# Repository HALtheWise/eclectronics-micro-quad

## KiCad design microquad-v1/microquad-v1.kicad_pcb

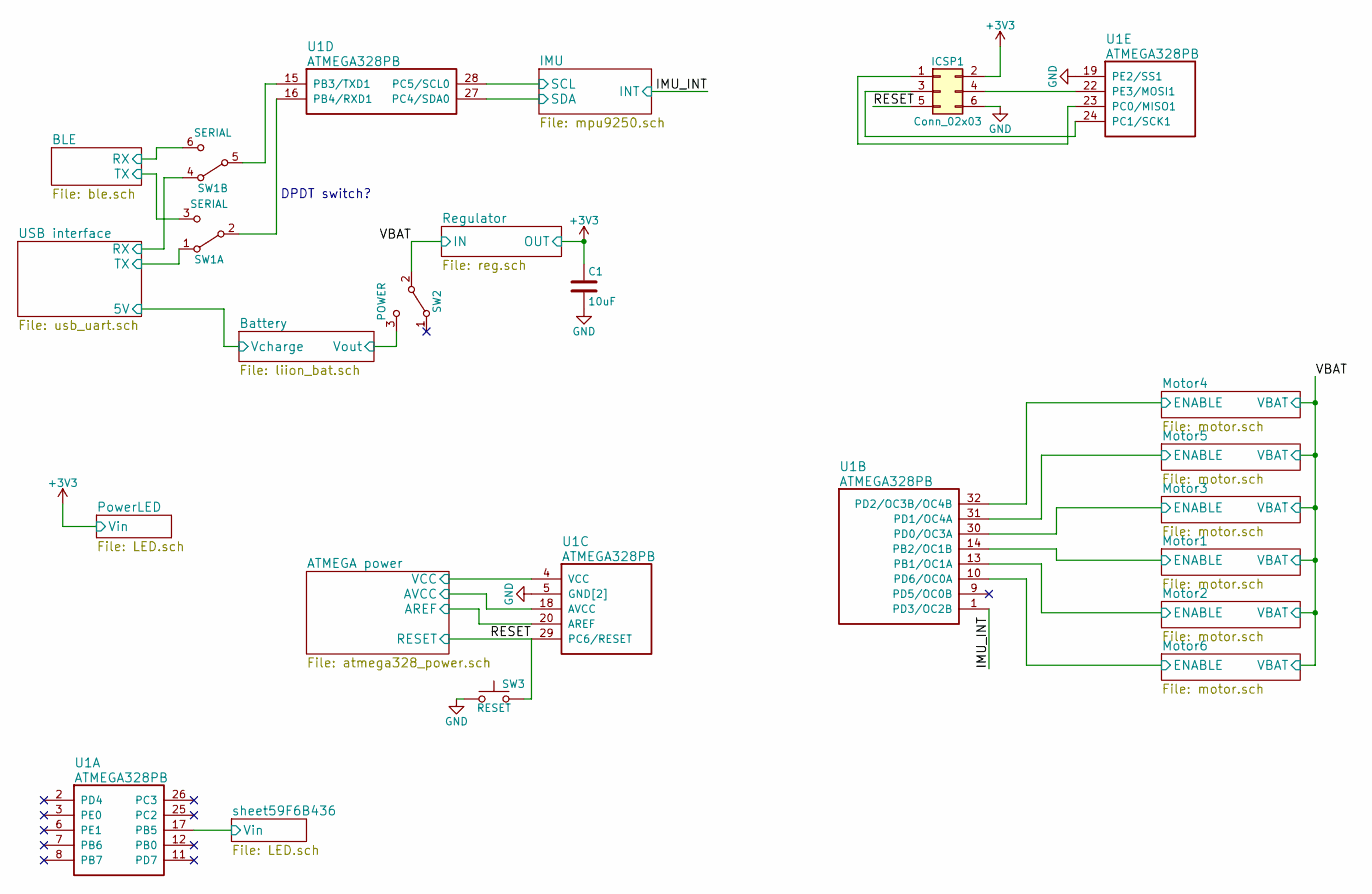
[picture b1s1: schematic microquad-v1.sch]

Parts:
C1: 10uF; C_0805
ICSP1: Conn_02x03; Pin_Header_Straight_2x03_Pitch2.54mm
SW1: SERIAL; quad_switch
SW2: POWER; quad_switch
SW3: RESET; SW_SPST_B3U-1000P
U1: ATMEGA328PB; TQFP-32_7x7mm_Pitch0.8mm

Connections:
+3V3: C1.1, ICSP1.2, U1.4 (VCC), U1.18 (AVCC), U1.20 (AREF); also elsewhere on the board
/BLE/RX: SW1.6 (C); also elsewhere on the board
/BLE/TX: SW1.3 (C); also elsewhere on the board
/Battery/Vout: SW2.3 (C); also elsewhere on the board
/IMU/SCL: U1.28 (PC5/SCL0); also elsewhere on the board
/IMU/SDA: U1.27 (PC4/SDA0); also elsewhere on the board
/IMU_INT: U1.1 (PD3/OC2B); also elsewhere on the board
/Motor1/ENABLE: U1.14 (PB2/OC1B); also elsewhere on the board
/Motor2/ENABLE: U1.13 (PB1/OC1A); also elsewhere on the board
/Motor3/ENABLE: U1.30 (PD0/OC3A); also elsewhere on the board
/Motor4/ENABLE: U1.32 (PD2/OC3B/OC4B); also elsewhere on the board
/Motor5/ENABLE: U1.31 (PD1/OC4A); also elsewhere on the board
/Motor6/ENABLE: U1.10 (PD6/OC0A); also elsewhere on the board
/RESET: ICSP1.5, SW3.2, U1.29 (PC6/RESET); also elsewhere on the board
/USB interface/RX: SW1.4 (A); also elsewhere on the board
/USB interface/TX: SW1.1 (A); also elsewhere on the board
/VBAT: SW2.2 (B); also elsewhere on the board
/sheet59F6B436/Vin: U1.17 (PB5); also elsewhere on the board
GND: C1.2, ICSP1.6, SW3.1, U1.5 (GND[2]), U1.19 (PE2/SS1), U1.21 (GND[2]); also elsewhere on the board
unnamed: ICSP1.1, U1.23 (PC0/MISO1)
unnamed: ICSP1.3, U1.24 (PC1/SCK1)
unnamed: ICSP1.4, U1.22 (PE3/MOSI1)
unnamed: SW1.2 (B), U1.16 (PB4/RXD1)
unnamed: SW1.5 (B), U1.15 (PB3/TXD1)

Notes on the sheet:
DPDT switch?

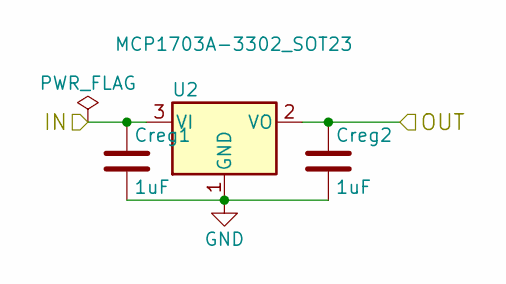
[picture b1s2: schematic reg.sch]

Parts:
Creg1, Creg2: 1uF; C_0603
U2: MCP1703A-3302_SOT23; SOT-23

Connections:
+3V3: Creg2.1, U2.2 (VO); also elsewhere on the board
/VBAT: Creg1.1, U2.3 (VI); also elsewhere on the board
GND: Creg1.2, Creg2.2, U2.1 (GND); also elsewhere on the board

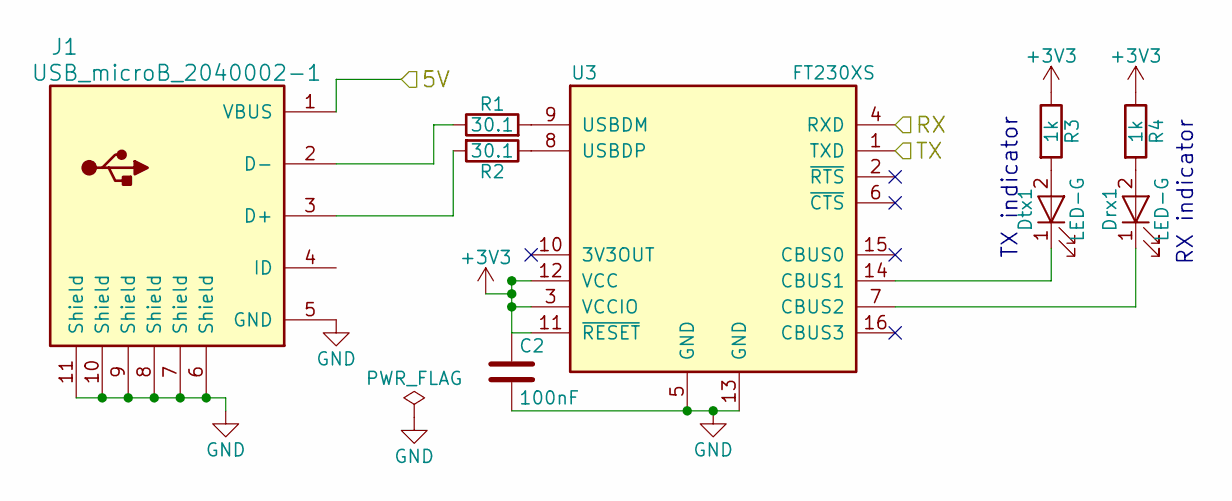
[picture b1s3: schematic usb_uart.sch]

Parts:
C2: 100nF; C_0603
Drx1: LED-G; LED_0805
Dtx1: LED-G; LED_0805
J1: USB_microB_2040002-1
R1, R2: 30.1; R_0603
R3, R4: 1k; R_0603
U3: FT230XS; SSOP-16_3.9x4.9mm_Pitch0.635mm

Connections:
+3V3: C2.1, R3.1, R4.1, U3.3 (VCCIO), U3.11 (~RESET), U3.12 (VCC); also elsewhere on the board
/USB interface/5V: J1.1 (VBUS); also elsewhere on the board
/USB interface/RX: U3.4 (RXD); also elsewhere on the board
/USB interface/TX: U3.1 (TXD); also elsewhere on the board
GND: C2.2, J1.5 (GND), J1.6 (Shield), J1.7 (Shield), J1.8 (Shield), J1.9 (Shield), J1.10 (Shield), J1.11 (Shield), U3.5 (GND), U3.13 (GND); also elsewhere on the board
unnamed: Drx1.1 (K), U3.7 (CBUS2)
unnamed: Drx1.2 (A), R4.2
unnamed: Dtx1.1 (K), U3.14 (CBUS1)
unnamed: Dtx1.2 (A), R3.2
unnamed: J1.2 (D-), R1.1
unnamed: J1.3 (D+), R2.2
unnamed: R1.2, U3.9 (USBDM)
unnamed: R2.1, U3.8 (USBDP)

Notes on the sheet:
RX indicator
TX indicator

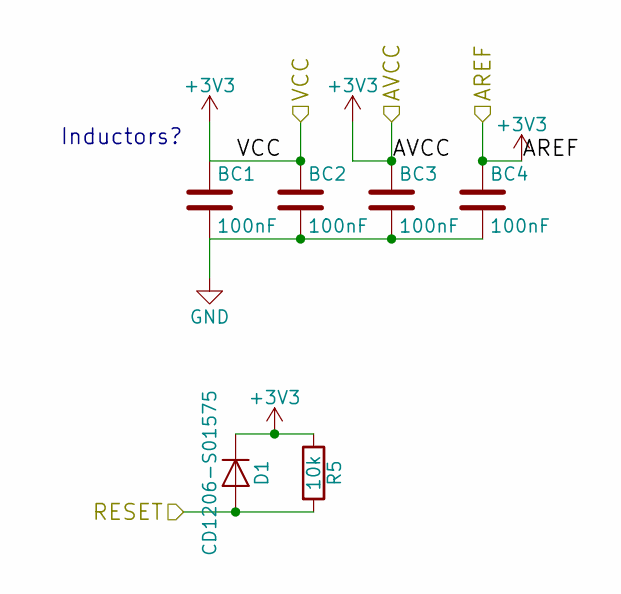
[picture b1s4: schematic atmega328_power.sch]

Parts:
BC1, BC2, BC3, BC4: 100nF; C_0603
D1: CD1206-S01575; C_0402
R5: 10k; R_0603

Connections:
+3V3: BC1.1, BC2.1, BC3.1, BC4.1, D1.1 (K), R5.1; also elsewhere on the board
/RESET: D1.2 (A), R5.2; also elsewhere on the board
GND: BC1.2, BC2.2, BC3.2, BC4.2; also elsewhere on the board

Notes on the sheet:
Inductors?

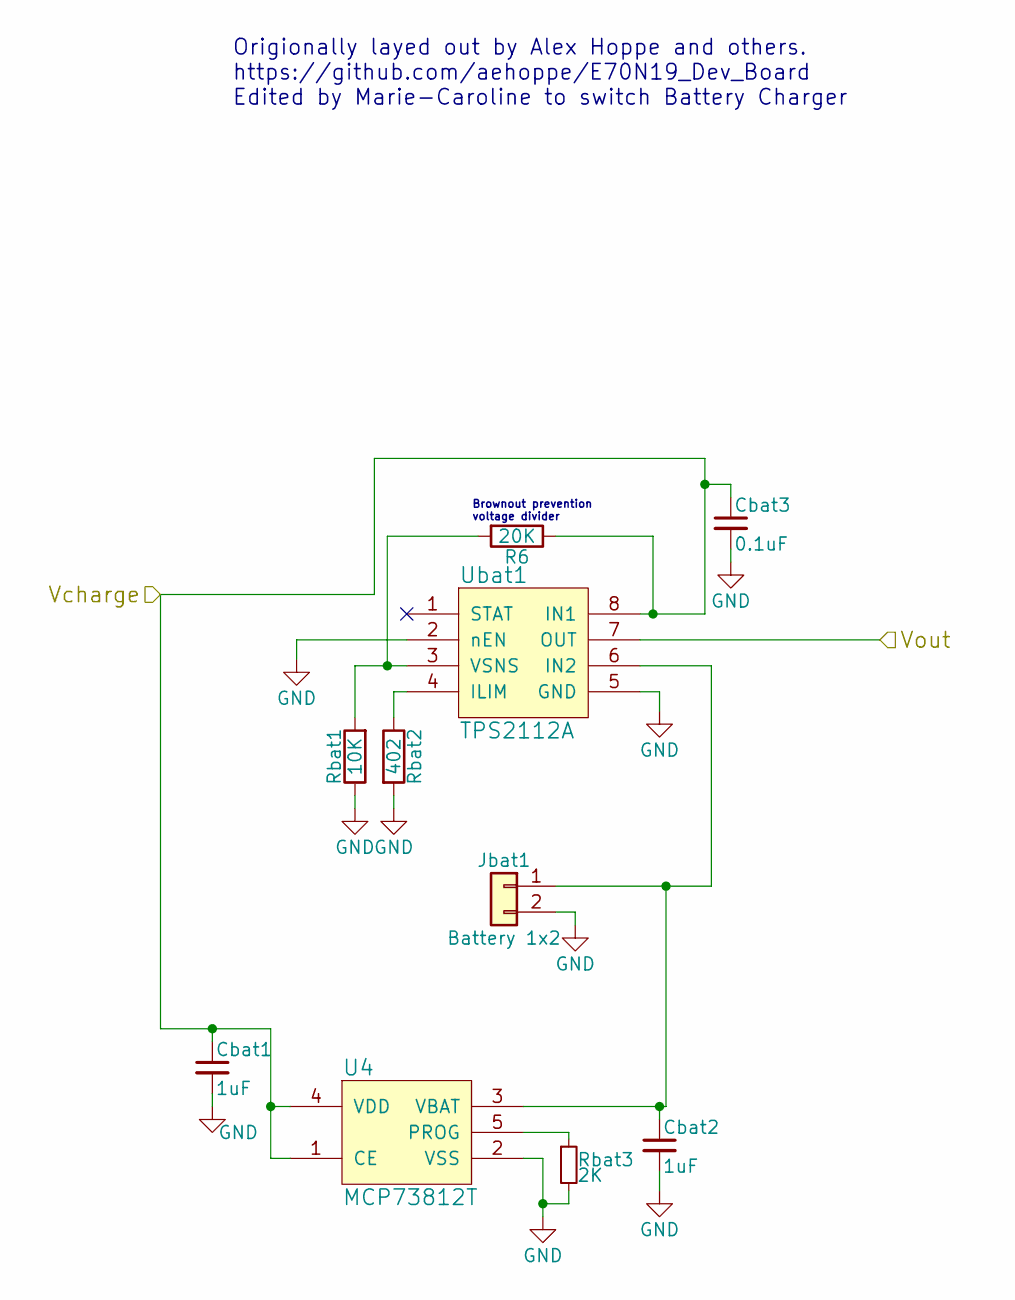
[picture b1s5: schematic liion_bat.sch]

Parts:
Cbat1, Cbat2: 1uF; C_0603
Cbat3: 0.1uF; C_0603
Jbat1: Battery 1x2; JST_PH_S2B-PH-SM4-TB_02x2.00mm_Angled
R6: 20K; R_0603
Rbat1: 10K; R_0603
Rbat2: 402; R_0603
Rbat3: 2K; R_0603
U4: MCP73812T; SOT-23
Ubat1: TPS2112A; TSSOP-8_4.4x3mm_Pitch0.65mm

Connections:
/Battery/Vout: Ubat1.7 (OUT); also elsewhere on the board
/USB interface/5V: Cbat1.1, Cbat3.1, R6.1, U4.1 (CE), U4.4 (VDD), Ubat1.8 (IN1); also elsewhere on the board
GND: Cbat1.2, Cbat2.2, Cbat3.2, Jbat1.2, Rbat1.1, Rbat2.2, Rbat3.2, U4.2 (VSS), Ubat1.2 (nEN), Ubat1.5 (GND); also elsewhere on the board
unnamed: Cbat2.1, Jbat1.1, U4.3 (VBAT), Ubat1.6 (IN2)
unnamed: R6.2, Rbat1.2, Ubat1.3 (VSNS)
unnamed: Rbat2.1, Ubat1.4 (ILIM)
unnamed: Rbat3.1, U4.5 (PROG)

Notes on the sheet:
Brownout prevention voltage divider
Origionally layed out by Alex Hoppe and others. https://github.com/aehoppe/E70N19_Dev_Board Edited by Marie-Caroline to switch Battery Charger

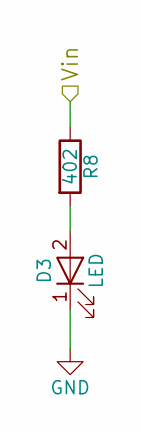
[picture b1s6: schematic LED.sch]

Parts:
D2: LED; LED_0805
R7: 402; R_0603

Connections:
+3V3: R7.1; also elsewhere on the board
GND: D2.1 (K); also elsewhere on the board
unnamed: D2.2 (A), R7.2

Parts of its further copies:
D3: LED; LED_0805
R8: 402; R_0603

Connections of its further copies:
/sheet59F6B436/Vin: R8.1; also elsewhere on the board
GND: D3.1 (K); also elsewhere on the board
unnamed: D3.2 (A), R8.2

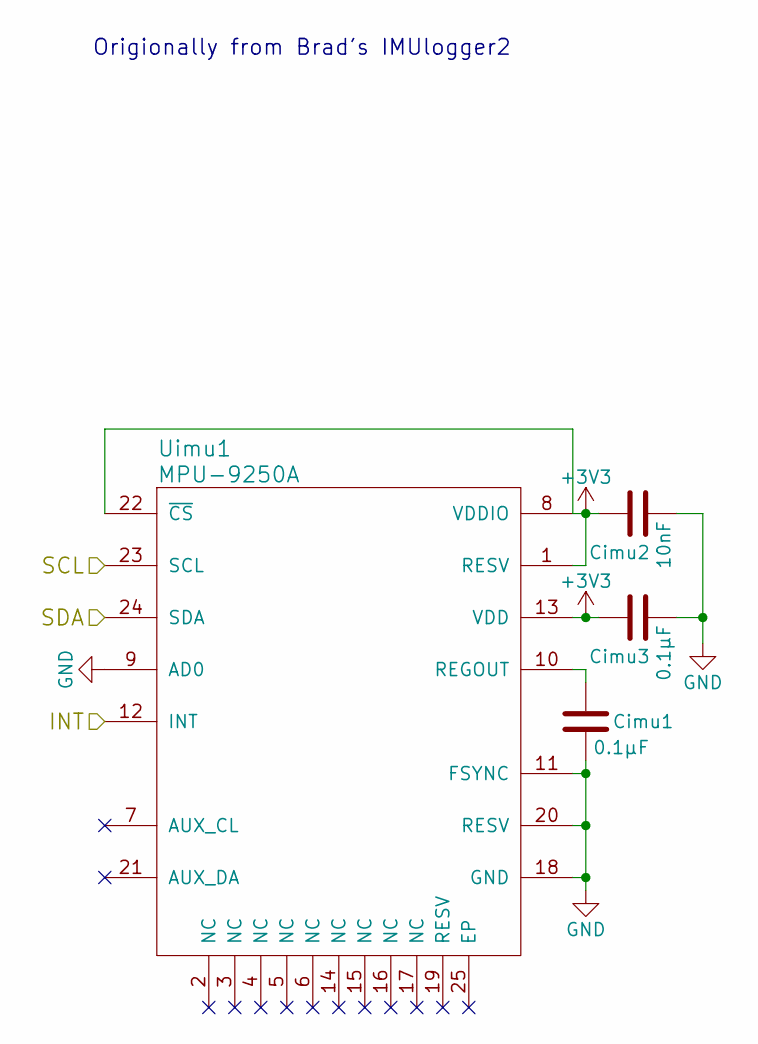
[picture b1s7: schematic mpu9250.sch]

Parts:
Cimu1, Cimu3: 0.1µF; C_0603
Cimu2: 10nF; C_0603
Uimu1: MPU-9250A; QFN40P300X300X105-25N

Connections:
+3V3: Cimu2.1, Cimu3.1, Uimu1.1 (RESV), Uimu1.8 (VDDIO), Uimu1.13 (VDD), Uimu1.22 (~CS); also elsewhere on the board
/IMU/SCL: Uimu1.23 (SCL); also elsewhere on the board
/IMU/SDA: Uimu1.24 (SDA); also elsewhere on the board
/IMU_INT: Uimu1.12 (INT); also elsewhere on the board
GND: Cimu1.2, Cimu2.2, Cimu3.2, Uimu1.9 (AD0), Uimu1.11 (FSYNC), Uimu1.18 (GND), Uimu1.20 (RESV); also elsewhere on the board
unnamed: Cimu1.1, Uimu1.10 (REGOUT)

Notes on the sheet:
Origionally from Brad's IMUlogger2

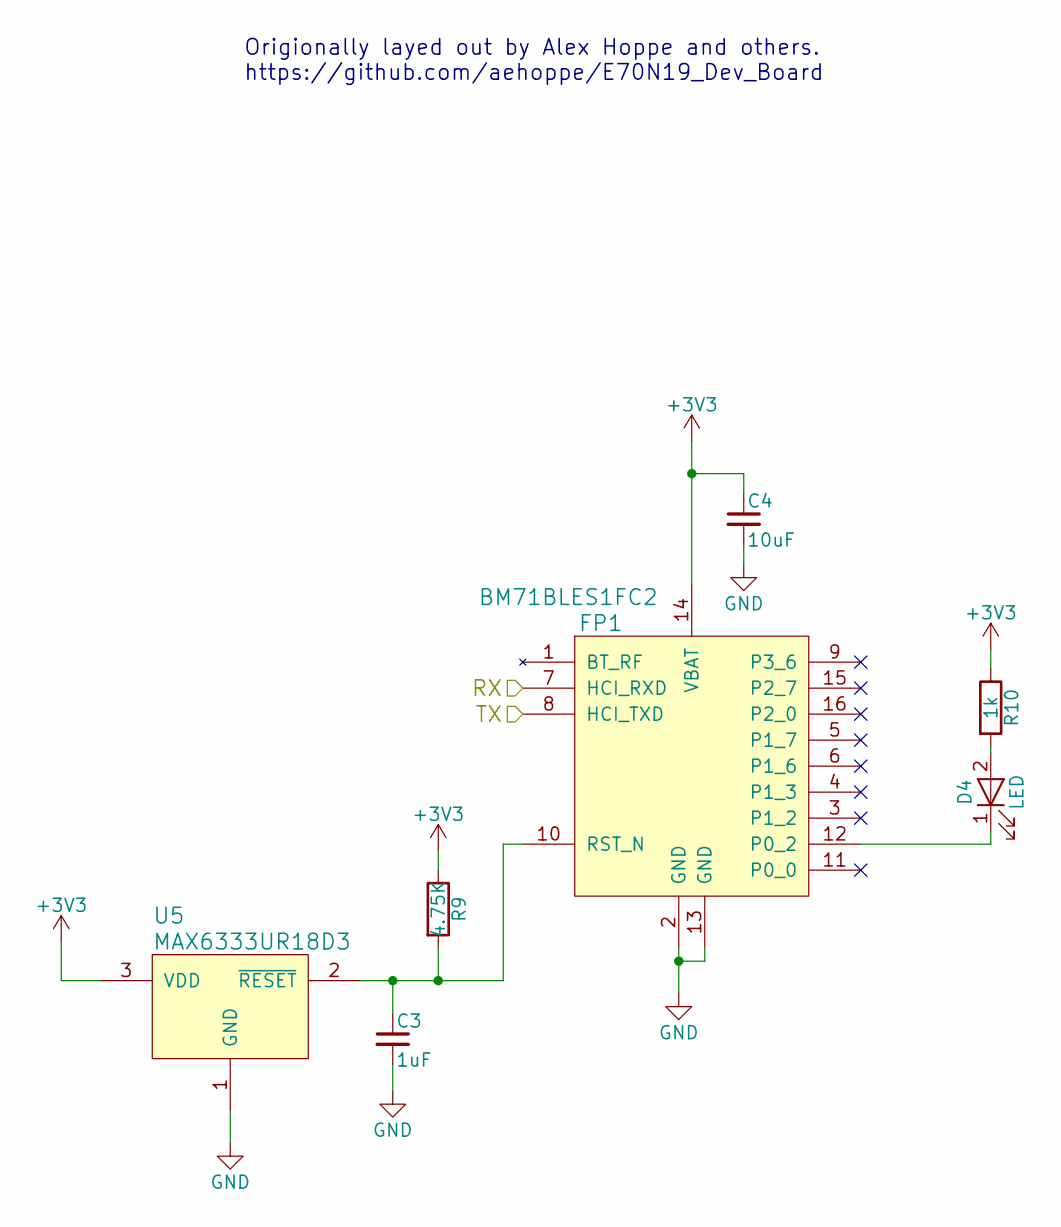
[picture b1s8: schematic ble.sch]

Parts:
C3: 1uF; C_0603
C4: 10uF; C_0805
D4: LED; LED_0805
FP1: BM71BLES1FC2
R9: 4.75K; R_0603
R10: 1k; R_0603
U5: MAX6333UR18D3; SOT-23

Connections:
+3V3: C4.1, FP1.14 (VBAT), R9.1, R10.1, U5.3 (VDD); also elsewhere on the board
/BLE/RX: FP1.7 (HCI_RXD); also elsewhere on the board
/BLE/TX: FP1.8 (HCI_TXD); also elsewhere on the board
GND: C3.2, C4.2, FP1.2 (GND), FP1.13 (GND), U5.1 (GND); also elsewhere on the board
unnamed: C3.1, FP1.10 (RST_N), R9.2, U5.2 (~RESET)
unnamed: D4.1 (K), FP1.12 (P0_2)
unnamed: D4.2 (A), R10.2

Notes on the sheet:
Origionally layed out by Alex Hoppe and others. https://github.com/aehoppe/E70N19_Dev_Board

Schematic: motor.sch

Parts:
C10: 10uF; C_0805
D5: BAS521LP-7; D_SOD-123F
D6: DNP; D_2114
M6: Motor_DC; quad_motor_v1
Q1: Q_NMOS_GSD; SOT-23

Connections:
/Motor1/ENABLE: Q1.1 (G); also elsewhere on the board
/VBAT: C10.2, D5.1 (K), M6.1 (+); also elsewhere on the board
GND: C10.1, D6.2 (A), Q1.2 (S); also elsewhere on the board

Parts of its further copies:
C5, C6, C7, C8, C9: 10uF; C_0805
D7, D9, D11, D13, D15: BAS521LP-7; D_SOD-123F
D8, D10, D12, D14, D16: DNP; D_2114
M1, M2, M3, M4, M5: Motor_DC; quad_motor_v1
Q2, Q3, Q4, Q5, Q6: Q_NMOS_GSD; SOT-23

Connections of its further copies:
/Motor2/ENABLE: Q2.1 (G); also elsewhere on the board
/Motor3/ENABLE: Q3.1 (G); also elsewhere on the board
/Motor4/ENABLE: Q4.1 (G); also elsewhere on the board
/Motor5/ENABLE: Q5.1 (G); also elsewhere on the board
/Motor6/ENABLE: Q6.1 (G); also elsewhere on the board
/VBAT: C5.2, C6.2, C7.2, C8.2, C9.2, D7.1 (K), D9.1 (K), D11.1 (K), D13.1 (K), D15.1 (K), M1.1 (+), M2.1 (+), M3.1 (+), M4.1 (+), M5.1 (+); also elsewhere on the board
GND: C5.1, C6.1, C7.1, C8.1, C9.1, D8.2 (A), D10.2 (A), D12.2 (A), D14.2 (A), D16.2 (A), Q2.2 (S), Q3.2 (S), Q4.2 (S), Q5.2 (S), Q6.2 (S); also elsewhere on the board
unnamed: D7.2 (A), D8.1 (K), M2.2 (-), Q2.3 (D)
unnamed: D9.2 (A), D10.1 (K), M3.2 (-), Q3.3 (D)
unnamed: D11.2 (A), D12.1 (K), M4.2 (-), Q4.3 (D)
unnamed: D13.2 (A), D14.1 (K), M5.2 (-), Q5.3 (D)

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
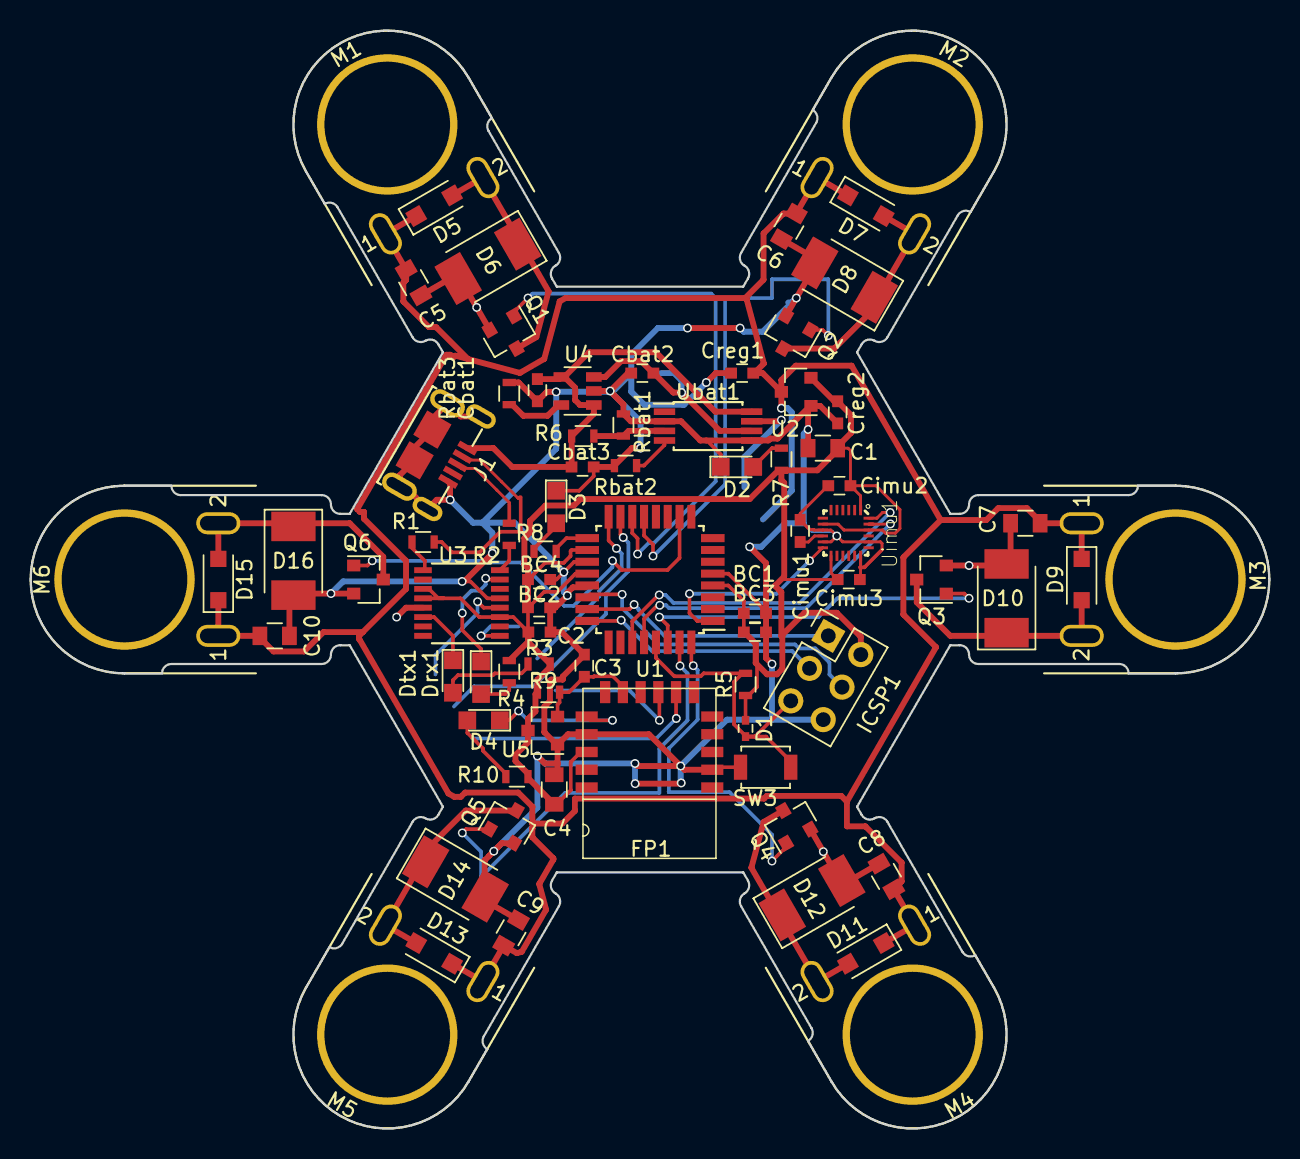
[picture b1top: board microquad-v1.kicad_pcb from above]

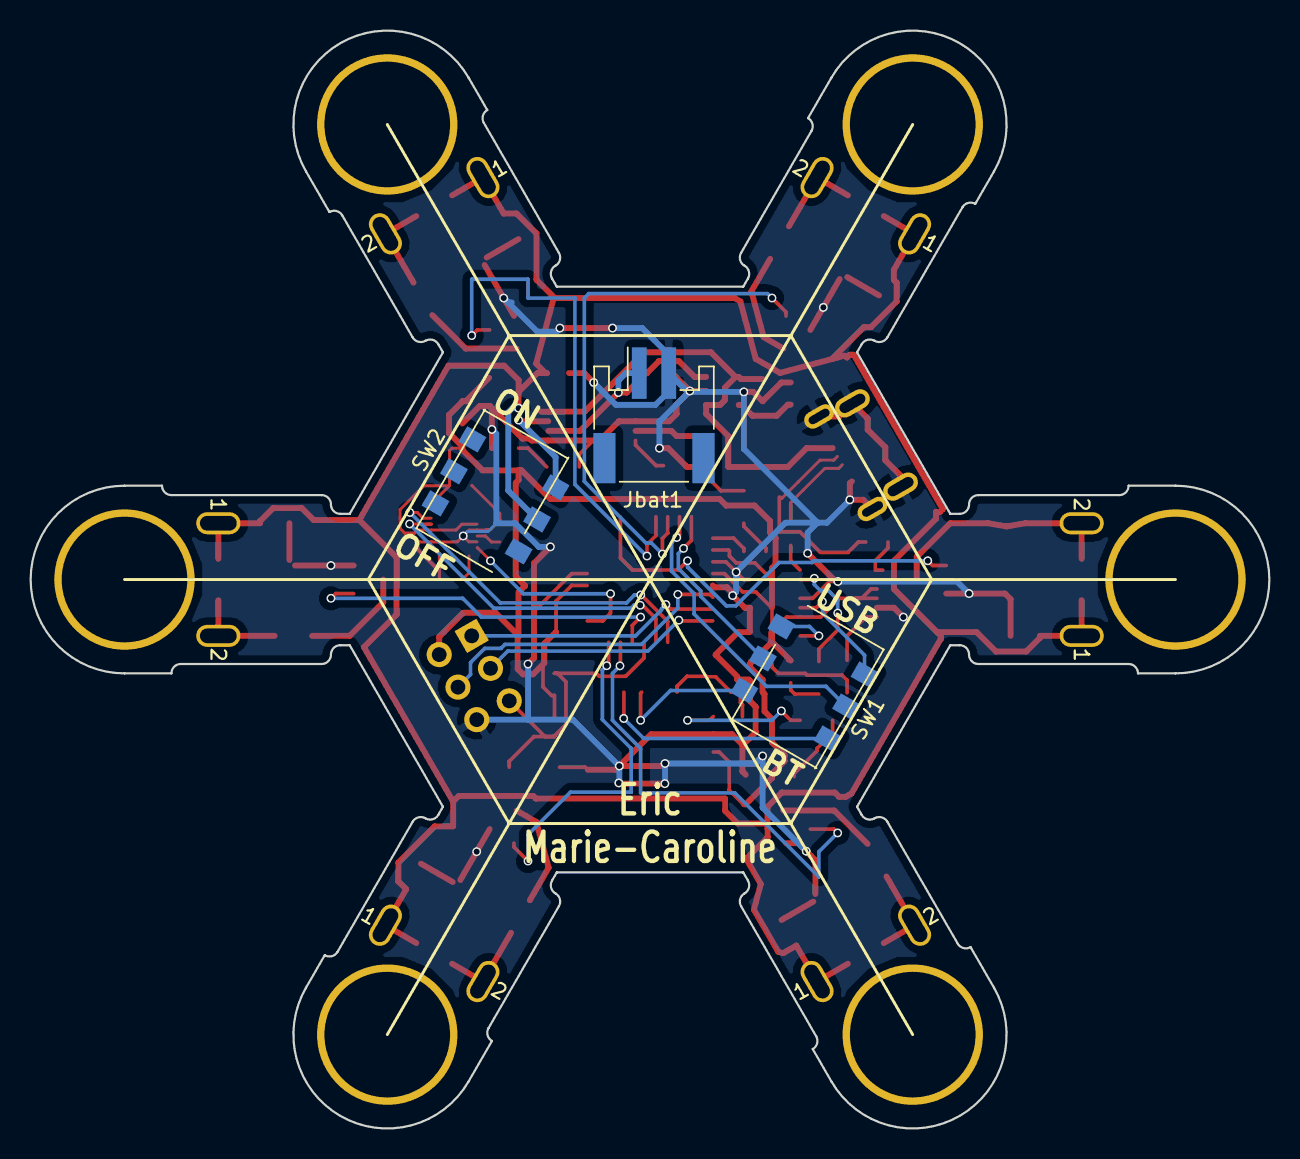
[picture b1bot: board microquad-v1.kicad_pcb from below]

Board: 2 copper layers, 83.8 x 74.3 mm, 79 parts (3 on the bottom side), 49 nets.

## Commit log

2017-10-26 Added gitignore and template project
2017-10-26 Added proposal
2017-10-26 Added 3V3 regulator and USB UART schematics from Eric's Project 2
2017-10-26 More libraries
2017-10-26 Added first version of kipart
2017-10-28 Added Hoppe's battery circuit
2017-10-28 Labeled Battery
2017-10-29 Added MPU9250 from Brad's Imulogger
2017-10-29 Brought in BLE module from Hoppe's project
2017-10-29 Add power switch
2017-10-29 Joe fixed merge
2017-10-29 Double checked and hooked up connections for BLE Added Power and Pin 12 LED
2017-10-29 Changed IMU to I2C pins
2017-10-29 Fixed imported IMU sheet
2017-10-29 Add new battery sub-schematic with new battery charger MCP73812
2017-10-29 Added motors
2017-10-29 Wired in motors
2017-10-29 Switched battery and merged some more stuff
2017-10-30 Add switch, LEDs, and no connector marks (probably still missing some, I'm not sure what all you still need
2017-10-30 Wired in IMU
2017-10-30 Moved LED to pin PB5
2017-10-30 Changed LED resistor values
2017-10-30 Added reset button
2017-10-30 Added IMU interrupt
2017-10-30 Changed switches to SPDT to prevent erroneous assignment
2017-10-30 Aesthetic rearrangement
2017-10-30 Fixed DRC errors (the ladybug is now happy)
2017-10-30 Notes from schematic review
2017-10-30 Changed to DPDT switches
2017-10-30 Added bypass diodes and extracted motors into separate schematic
2017-10-31 Added layout for transistor
2017-10-31 Added footprint library for USB connector and BT chip
2017-10-31 Added v1 layout for motor
2017-11-01 Finished footprint work 10/31
2017-11-03 Finished in-class work 10/2
2017-11-03 Deleted temp file
2017-11-03 Finished footprints for diodes
2017-11-03 Started layout
2017-11-03 All non-motor components placed on board
2017-11-03 Initial power routing to all major chips
2017-11-03 Handled some wire routing for IMU
2017-11-03 Finished routing most of the top side
2017-11-03 Added ground pour
2017-11-04 Made a pretty array of motors
2017-11-04 Fixed motor component labels and reimported netlist
2017-11-04 Started compacting components
2017-11-04 Change motor component references
2017-11-04 Additional compaction
2017-11-05 Edgecuts
2017-11-05 Finished placing components more tightly
2017-11-05 Merged new netlist
2017-11-06 Add tracks on arms and connect VBAT, requires DRC violations... (not actual violations, KiCad just thinks they are)
2017-11-06 Fixed VBAT connections
2017-11-06 Fixed disconnects around the board
2017-11-06 Ladybug is satisfied
2017-11-06 Better bridges
2017-11-06 Changed visibility of layers
2017-11-06 Silkscreen work on front
2017-11-06 Add outer silkscreen
2017-11-06 Rerouted vbat and moved USB
2017-11-06 Ready to submit
2017-11-08 Removed copper pour from underneath bluetooth module
2017-11-17 Printed fabrication drawing
